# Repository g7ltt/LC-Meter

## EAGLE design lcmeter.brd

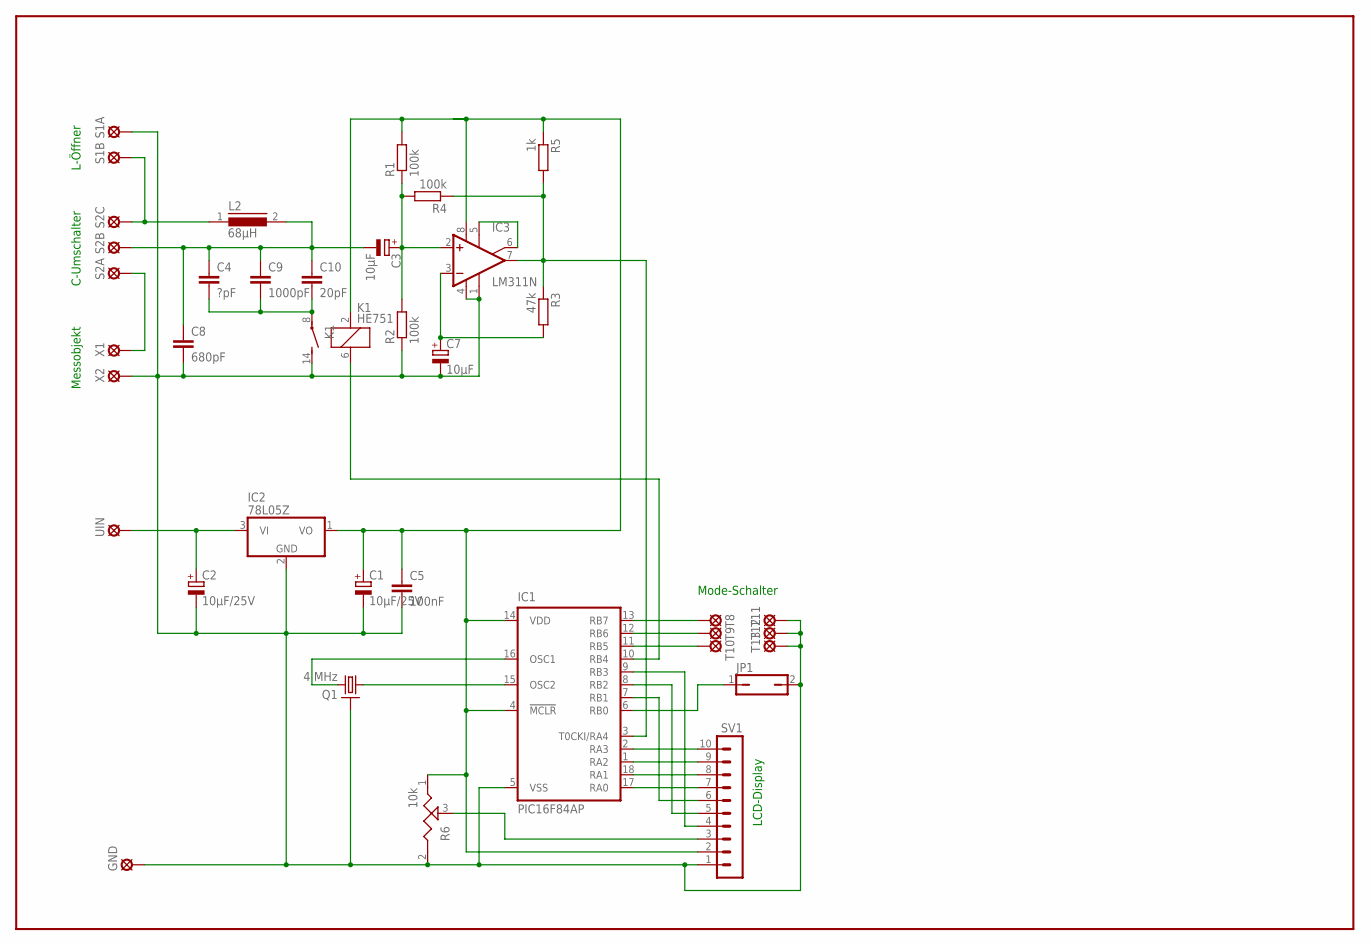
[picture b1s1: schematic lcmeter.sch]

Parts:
C1, C2: 10µF/25V; E2,5-5
C3, C7: 10µF; E5-10,5
C4: ?pF; C150-054X183
C5: 100nF; C050-050X075
C8: 680pF; C150-054X183
C9: 1000pF; C150-054X183
C10: 20pF; C150-054X183
GND: LSP10
IC1: PIC16F84AP; DIL18
IC2: 78L05Z; TO92
IC3: LM311N; DIL08
JP1: JP1Q; JP1
K1: HE751
L2: 68µH; MESC26
Q1: 4 MHz; RES3PIN
R1, R2, R4: 100k; 0309/12
R3: 47k; 0309/12
R5: 1k; 0309/12
R6: 10k; PT-10
S1A, S1B, S2A, S2B, S2C: LSP10
SV1: MA10-1
T8, T9, T10, T11, T12, T13: LSP10
UIN: LSP10
X1: LCx1; LSP10
X2: LSP10

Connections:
+5V: C1.+, C5.1, IC1.4 (!MCLR), IC1.14 (VDD), IC2.1 (VO), IC3.8 (V+), K1.2 (1), R1.2, R5.1, R6.1, SV1.2
GND: C1.-, C2.-, C5.2, C7.-, C8.2, GND.MP, IC1.5 (VSS), IC2.2 (GND), IC3.1 (GND), IC3.4 (V-), JP1.2, K1.14 (S), Q1.2 (3), R2.1, R6.2, S1A.MP, SV1.1, T11.MP, T12.MP, T13.MP, X2.MP
unnamed: IC1.2 (RA3), SV1.10
unnamed: IC1.1 (RA2), SV1.9
unnamed: IC1.18 (RA1), SV1.8
unnamed: IC1.17 (RA0), SV1.7
unnamed: IC1.7 (RB1), SV1.6
unnamed: IC1.8 (RB2), SV1.5
unnamed: IC1.9 (RB3), SV1.4
unnamed: L2.1, S1B.MP, S2C.MP
unnamed: C3.+, IC3.2 (+IN), R1.1, R2.2, R4.2
unnamed: C2.+, IC2.3 (VI), UIN.MP
unnamed: IC1.15 (OSC2), Q1.1
unnamed: IC1.16 (OSC1), Q1.3 (2)
unnamed: IC1.6 (RB0), JP1.1
unnamed: C7.+, IC3.3 (-IN), R3.2
unnamed: IC3.5 (ON), IC3.6 (ON/STR)
unnamed: IC1.3 (T0CKI/RA4), IC3.7 (OUT), R3.1, R4.1, R5.2
unnamed: C3.-, C4.1, C8.1, C9.1, C10.1, L2.2, S2B.MP
unnamed: C4.2, C9.2, C10.2, K1.8
unnamed: IC1.10 (RB4), K1.6 (2)
unnamed: S2A.MP, X1.MP
unnamed: R6.3, SV1.3
unnamed: IC1.13 (RB7), T8.MP
unnamed: IC1.12 (RB6), T9.MP
unnamed: IC1.11 (RB5), T10.MP

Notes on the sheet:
LCD-Display
Mode-Schalter
Messobjekt
L-Öffner
C-Umschalter

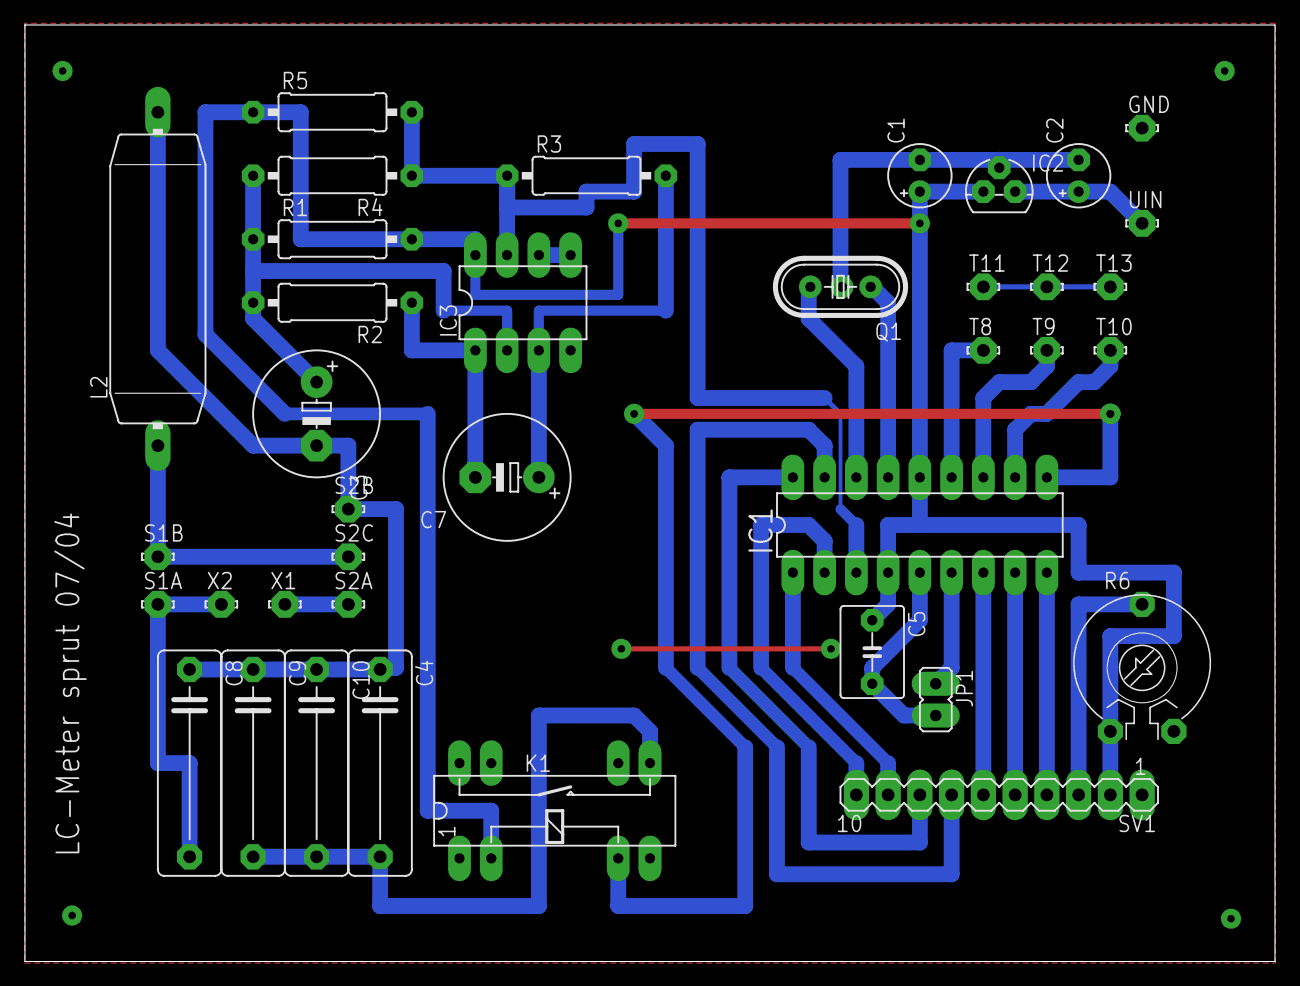
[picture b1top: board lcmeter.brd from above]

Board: 2 copper layers, 100.0 x 74.9 mm, 38 parts (0 on the bottom side), 26 nets.
